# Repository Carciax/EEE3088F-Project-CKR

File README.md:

# EEE3088F-Project-CKR
#Group number 12
# Students: 
Cameron Clark, CLRCAM007; 
Kian Frassek, FRSKIA001; 
Robert Dugmore, DGMROB001; 

## Table of contents
* Description of HAT
* Getting started
  * Introduction
  * Ordering and assembling a HAT
  * Other hardware requirements
  * Hardware connection
  * Software requirements
  * Basic operation of HAT
  * Licensing

# Description of HAT

This sensor PCB HAT connects to an STM32F0 microcontroller and adds additional sensing functionality in the form of an ambient light sensor, a temperature and humidity sensor, an thermistor, and a potentiometer (which could be connected to some form of mechanical sensing system, e.g., a wind vane). The board can be powered directly from USB, or can be powered by an 18650 battery.

# Getting started

## Introduction

This sensor HAT aims to expand the functionality of an STM32F0 microcontroller by adding various sensors. This getting started guide will go over the minimum hardware and software requirements to connect the HAT and start taking measurements.

## Ordering and assembling a HAT

### Ordering from JLC PCB

The HAT has been designed to meet the specifications from JLC PCB (jlcpcb.com). To order a HAT:
* Go to JLC's website (jlcpcb.com)
* Request a quote
* Upload "Final Submission/GROUP12_gerber.zip" as your gerber files
* Select the board specifications (e.g., colour, finish, etc.) as you like. The default options are a reasonable choice.
* Select the option for single sided assembly
* Follow the website instructions until you are prompted to upload a position file and BOM.
* The position file is "Final Submission/GROUP12_position.cpl", and the BOM file is "FINAL_SUBMISSION/GROUP12_bom.csv".
* When asked about footprints that do not have a part number assigned, select "do not place"
* Follow any further instructions from the website for payment and delivery

### Ordering from another board house

If ordering from JLC PCB is not an option for you, you can use the same gerber, position and BOM files to order your HAT from another board house. However, please note the following:
* The HAT may not meet the specifications of another board house.
* The BOM file is unlikely to be in the correct format for another board house.
* The BOM file is unlikely to contain references to the correct components from another board houses's stock; manual selection of components will probably be necessary.

### Additional steps

All male and female headers will have to be obtained and soldered on separately.

It is also recommended to keep track of the issues page of the github to see if there are any outstanding hardware issues with the current iteration of the HAT, which may require manual intervention to solve. 

## Other hardware requirements

### List of required hardware

In addition to the HAT, the following hardware is required:
* an STM32FO microcontoller, with pins connected to 2 1x24-pin male headers spaced -1.524 mm (0.6 in) apart
* A microUSB-B cable
* A 5V USB power supply
* Optional: An 18650 battery
* A computer with an available USB port running Linux or Windows

## Hardware connection

### Microcontroller

The microcontroller should be directly connected to the double-row of females headers labelled "J3". 

### Battery

The 18650 battery (if being used) can be placed directly into the battery holder, taking care to connect it with the correct polarity. The HAT will automatically cut battery power if the voltage drops too low, to protect the battery.

### USB (power supply and data transfer)

The HAT is powered (and the battery is charged) immediately when 5V power is received from the singular USB port. Connecting the USB to a computer enables the start of data transfer to the computer.

### Battery charging

The 18650 battery is charged by the 5V USB power supply. 
The HAT includes red and green charging LEDs. The red LED is powered when the battery is charging, and the green LED is powered when the battery is fully charged.

## Software requirements

### STM32F0 Firmware

The firmware from this repository takes measurements from all sensors at a soft-configurable regular interval. This will need to be uploaded to STM32F0 board.

### Required PC software

The default firmware outputs value over USB serial and requires no additional software.

## Basic operation of HAT

### Reading data on the pc

Data is saved to the EEPROM by default. To send all EEPROM data over the USB connection:
* Connect the USB
* Press switch 1
* LED 1 will flash until all data has been sent
* To abort, press switch 1 again.

### Configuring data read rate

Under normal operation, the HAT takes 1 reading every 60 seconds. This can be soft-configured as follows:
* Press switch 2
* LED 2 will start to flash
* Turn the potentiometer to a desired reading level
* Press 2 again to confirm

## Licensing
MIT License

Copyright (c) 2023 Kian Frassek, Cameron Clark, Robert Dugmore

Permission is hereby granted, free of charge, to any person obtaining a copy
of this software and associated documentation files (the "Software"), to deal
in the Software without restriction, including without limitation the rights
to use, copy, modify, merge, publish, distribute, sublicense, and/or sell
copies of the Software, and to permit persons to whom the Software is
furnished to do so, subject to the following conditions:

The above copyright notice and this permission notice shall be included in all
copies or substantial portions of the Software.

THE SOFTWARE IS PROVIDED "AS IS", WITHOUT WARRANTY OF ANY KIND, EXPRESS OR
IMPLIED, INCLUDING BUT NOT LIMITED TO THE WARRANTIES OF MERCHANTABILITY,
FITNESS FOR A PARTICULAR PURPOSE AND NONINFRINGEMENT. IN NO EVENT SHALL THE
AUTHORS OR COPYRIGHT HOLDERS BE LIABLE FOR ANY CLAIM, DAMAGES OR OTHER
LIABILITY, WHETHER IN AN ACTION OF CONTRACT, TORT OR OTHERWISE, ARISING FROM,
OUT OF OR IN CONNECTION WITH THE SOFTWARE OR THE USE OR OTHER DEALINGS IN THE
SOFTWARE.

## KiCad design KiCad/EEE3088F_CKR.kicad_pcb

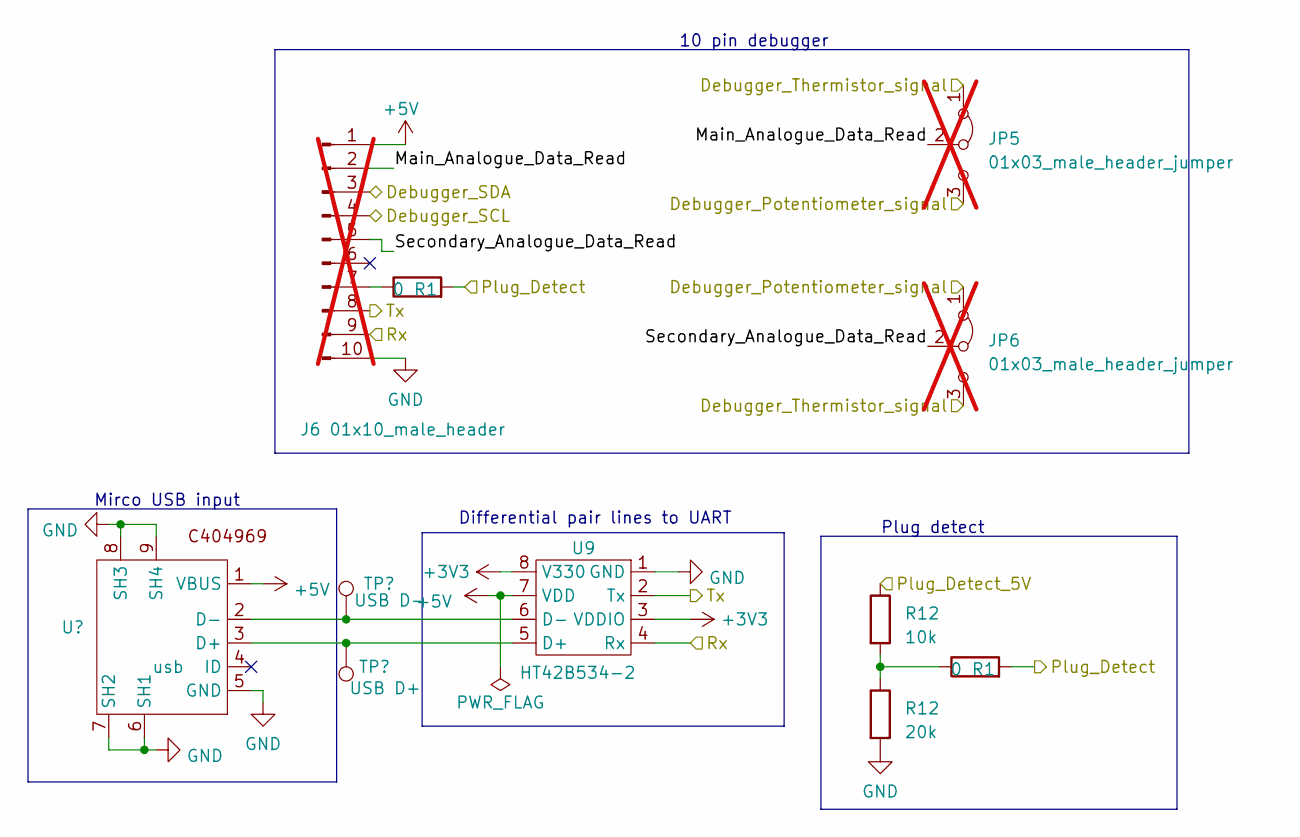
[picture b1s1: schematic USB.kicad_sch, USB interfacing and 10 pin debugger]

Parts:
J6: 01x10_male_header; PinHeader_1x10_P2.54mm_Vertical; not fitted
JP5, JP6: 01x03_male_header_jumper; PinHeader_1x03_P2.54mm_Vertical; not fitted
R1: 0; R0603; Part name 0603WAF0000T5E; JLC code C21189
R12: 20k; R0603; Part name 0603WAF2002T5E; JLC code C4184
TP21: USB D-; Testpoint
TP22: USB D+; Testpoint
U8: usb; MICRO-USB-SMD_MICROXNJ; Part name MicroXNJ; JLC code C404969
U9: HT42B534-2; SOP-8_L4.9-W3.9-P1.27-LS6.0-BL; Part name HT42B534-2; JLC code C493294

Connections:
+3V3: U9.3 (VDDIO), U9.8 (V330); also elsewhere on the board
+5V: J6.1, R1.2, U8.1 (VBUS), U9.7 (VDD); also elsewhere on the board
/Microcontroller/POT_uc: JP5.3 (B), JP6.1 (A); also elsewhere on the board
/Microcontroller/Rx: J6.8, U9.2 (Tx); also elsewhere on the board
/Microcontroller/SCL_uc: J6.4; also elsewhere on the board
/Microcontroller/SDA_uc: J6.3; also elsewhere on the board
/Microcontroller/THM_uc: JP5.1 (A), JP6.3 (B); also elsewhere on the board
/Microcontroller/Tx: J6.9, U9.4 (Rx); also elsewhere on the board
/USB/Main_Analogue_Data_Read: J6.2, JP5.2 (C)
/USB/Secondary_Analogue_Data_Read: J6.5, JP6.2 (C)
unnamed: TP22.1, U8.3 (D+), U9.5 (D+)
unnamed: TP21.1, U8.2 (D-), U9.6 (D-)

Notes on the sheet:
Plug detect
Differential pair lines to UART
10 pin debugger
Mirco USB input

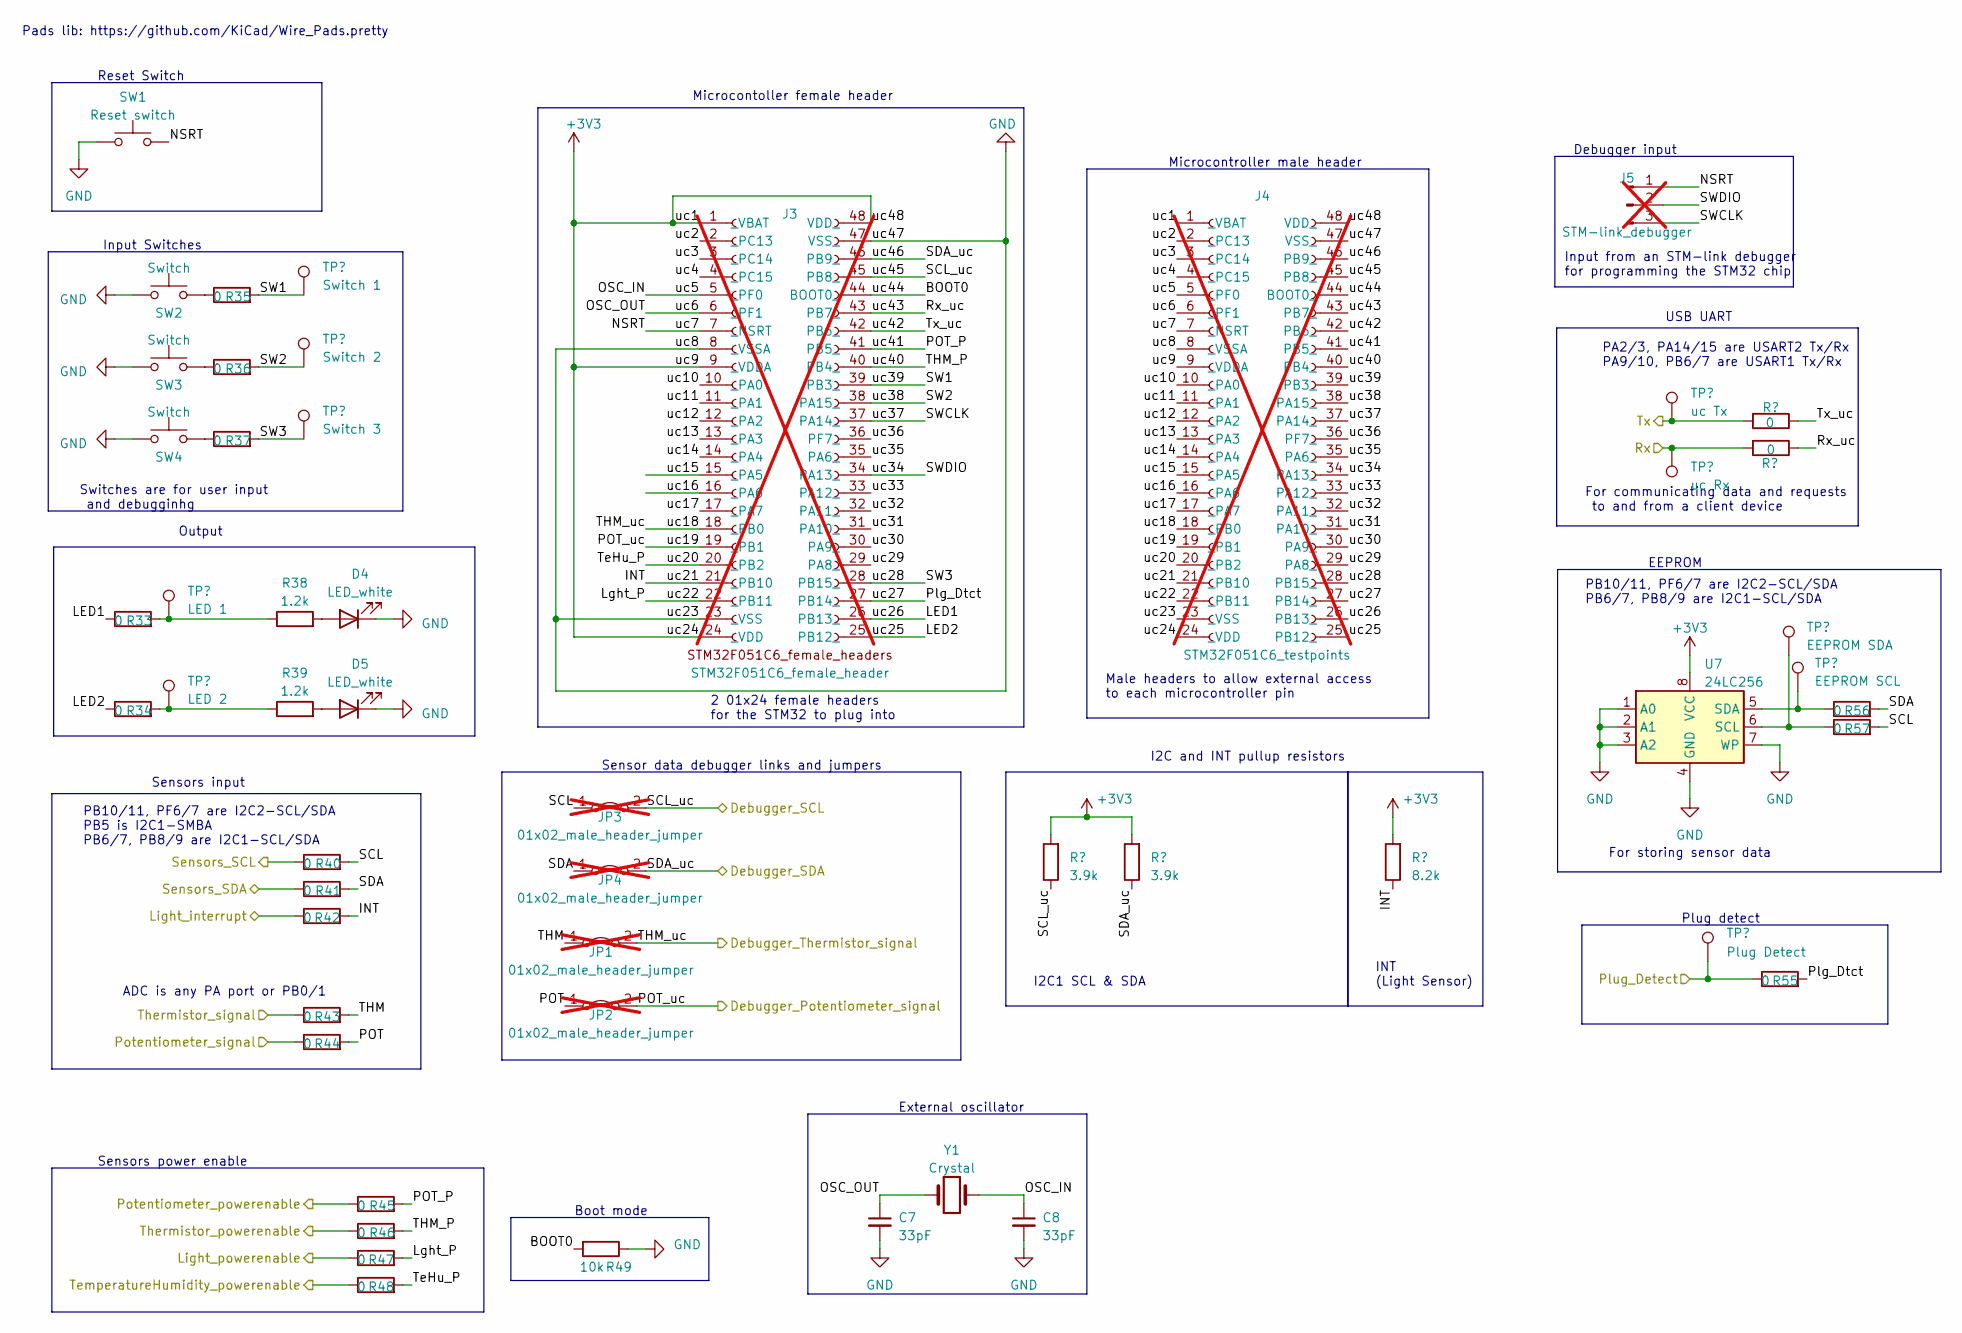
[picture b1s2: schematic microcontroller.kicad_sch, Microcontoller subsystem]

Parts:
C7, C8: 33pF; C0402; Part name 0402CG300J500NT; JLC code C1570
D4, D5: LED_white; LED0805-R-RD; Part name C34499; JLC code C34499
J3: STM32F051C6_female_header; not fitted
J4: STM32F051C6_testpoints; not fitted
J5: STM-link_debugger; PinHeader_1x03_P2.54mm_Vertical; not fitted
JP1, JP2, JP3, JP4: 01x02_male_header_jumper; PinHeader_1x02_P2.54mm_Vertical; not fitted
R33, R34, R35, R36, R37, R40, R41, R42, R43, R44, R45, R46, R47, R48, R53, R54, R55, R56, R57: 0; R0603; Part name 0603WAF0000T5E; JLC code C21189
R38, R39: 1.2k; R0805; Part name 0805W8F3300T5E; JLC code C17630
R49: 10k; R0805; Part name 0805W8F1002T5E; JLC code C17414
R50, R51: 3.9k; R0402; Part name 0402WGF3901TCE; JLC code C51721
R52: 8.2k; R0402; Part name 0402WGF8201TCE; JLC code C25924
SW1: Reset switch; SW-SMD_4P-L5.1-W5.1-P3.70-LS6.5-TL-2; Part name TS-1187A-B-A-B; JLC code C318884
SW2, SW3, SW4: Switch; SW-SMD_4P-L5.1-W5.1-P3.70-LS6.5-TL-2; Part name TS-1187A-B-A-B; JLC code C318884
TP11: LED 1; Testpoint
TP12: LED 2; Testpoint
TP13: Switch 1; Testpoint
TP14: Switch 2; Testpoint
TP15: Switch 3; Testpoint
TP16: uc Tx; Testpoint
TP17: uc Rx; Testpoint
TP18: Plug Detect; Testpoint
TP19: EEPROM SDA; Testpoint
TP20: EEPROM SCL; Testpoint
U7: 24LC256; PDIP-8_L9.3-W6.4-P2.54-LS7.6-BL; Part name 24LC256; JLC code C411624
Y1: Crystal; CRYSTAL-SMD_L11.5-W4.8-LS12.7; Part name X49SM8MSD2SC; JLC code C12674

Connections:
+3V3: J3.1 (_VBAT), J3.9 (_VDDA), J3.24 (_VDD), J3.48 (VDD_), J4.1 (_VBAT), J4.9 (_VDDA), J4.24 (_VDD), J4.48 (VDD_), R50.2, R51.2, R52.2, U7.8 (VCC); also elsewhere on the board
/Microcontroller/BOOT0: J3.44 (BOOT0_), J4.44 (BOOT0_), R49.2
/Microcontroller/INT: J3.21 (_PB10), J4.21 (_PB10), R42.2, R52.1
/Microcontroller/LED1: J3.26 (PB13_), J4.26 (PB13_), R33.1
/Microcontroller/LED2: J3.25 (PB12_), J4.25 (PB12_), R34.1
/Microcontroller/Lght_P: J3.22 (_PB11), J4.22 (_PB11), R47.2
/Microcontroller/Light_powerenable: R47.1; also elsewhere on the board
/Microcontroller/NSRT: J3.7 (_NSRT), J4.7 (_NSRT), J5.1, SW1.2
/Microcontroller/OSC_IN: C8.1, J3.5 (_PF0), J4.5 (_PF0), Y1.2
/Microcontroller/OSC_OUT: C7.1, J3.6 (_PF1), J4.6 (_PF1), Y1.1
/Microcontroller/POT: JP2.1 (A), R44.2
/Microcontroller/POT_P: J3.41 (PB5_), J4.41 (PB5_), R45.2
/Microcontroller/POT_uc: J3.19 (_PB1), J4.19 (_PB1), JP2.2 (B); also elsewhere on the board
/Microcontroller/Plg_Dtct: J3.27 (PB14_), J4.27 (PB14_), R55.2
/Microcontroller/Plug_Detect: R55.1, TP18.1; also elsewhere on the board
/Microcontroller/Potentiometer_powerenable: R45.1; also elsewhere on the board
/Microcontroller/Potentiometer_signal: R44.1; also elsewhere on the board
/Microcontroller/Rx: R54.2, TP17.1; also elsewhere on the board
/Microcontroller/Rx_uc: J3.43 (PB7_), J4.43 (PB7_), R54.1
/Microcontroller/SCL: JP3.1 (A), R40.2, R57.2
/Microcontroller/SCL_uc: J3.45 (PB8_), J4.45 (PB8_), JP3.2 (B), R50.1; also elsewhere on the board
/Microcontroller/SDA: JP4.1 (A), R41.2, R56.2
/Microcontroller/SDA_uc: J3.46 (PB9_), J4.46 (PB9_), JP4.2 (B), R51.1; also elsewhere on the board
/Microcontroller/SW1: J3.39 (PB3_), J4.39 (PB3_), R35.2, TP13.1
/Microcontroller/SW2: J3.38 (PA15_), J4.38 (PA15_), R36.2, TP14.1
/Microcontroller/SW3: J3.28 (PB15_), J4.28 (PB15_), R37.2, TP15.1
/Microcontroller/SWCLK: J3.37 (PA14_), J4.37 (PA14_), J5.3
/Microcontroller/SWDIO: J3.34 (PA13_), J4.34 (PA13_), J5.2
/Microcontroller/THM: JP1.1 (A), R43.2
/Microcontroller/THM_P: J3.40 (PB4_), J4.40 (PB4_), R46.2
/Microcontroller/THM_uc: J3.18 (_PB0), J4.18 (_PB0), JP1.2 (B); also elsewhere on the board
/Microcontroller/TeHu_P: J3.20 (_PB2), J4.20 (_PB2), R48.2
/Microcontroller/TemperatureHumidity_powerenable: R48.1; also elsewhere on the board
/Microcontroller/Thermistor_powerenable: R46.1; also elsewhere on the board
/Microcontroller/Thermistor_signal: R43.1; also elsewhere on the board
/Microcontroller/Tx: R53.2, TP16.1; also elsewhere on the board
/Microcontroller/Tx_uc: J3.42 (PB6_), J4.42 (PB6_), R53.1
/Microcontroller/uc2: J3.2 (_PC13), J4.2 (_PC13)
/Microcontroller/uc3: J3.3 (_PC14), J4.3 (_PC14)
/Microcontroller/uc4: J3.4 (_PC15), J4.4 (_PC15)
/Microcontroller/uc10: J3.10 (_PA0), J4.10 (_PA0)
/Microcontroller/uc11: J3.11 (_PA1), J4.11 (_PA1)
/Microcontroller/uc12: J3.12 (_PA2), J4.12 (_PA2)
/Microcontroller/uc13: J3.13 (_PA3), J4.13 (_PA3)
/Microcontroller/uc14: J3.14 (_PA4), J4.14 (_PA4)
/Microcontroller/uc15: J3.15 (_PA5), J4.15 (_PA5)
/Microcontroller/uc16: J3.16 (_PA6), J4.16 (_PA6)
/Microcontroller/uc17: J3.17 (_PA7), J4.17 (_PA7)
/Microcontroller/uc29: J3.29 (PA8_), J4.29 (PA8_)
/Microcontroller/uc30: J3.30 (PA9_), J4.30 (PA9_)
/Microcontroller/uc31: J3.31 (PA10_), J4.31 (PA10_)
/Microcontroller/uc32: J3.32 (PA11_), J4.32 (PA11_)
/Microcontroller/uc33: J3.33 (PA12_), J4.33 (PA12_)
/Microcontroller/uc35: J3.35 (PA6_), J4.35 (PA6_)
/Microcontroller/uc36: J3.36 (PF7_), J4.36 (PF7_)
/Sensors/Light_SCL: R40.1; also elsewhere on the board
/Sensors/Light_SDA: R41.1; also elsewhere on the board
/Sensors/Light_interrupt: R42.1; also elsewhere on the board
unnamed: D4.2 (A), R38.2
unnamed: D5.2 (A), R39.2
unnamed: R33.2, R38.1, TP11.1
unnamed: R34.2, R39.1, TP12.1
unnamed: R35.1, SW2.2
unnamed: R36.1, SW3.2
unnamed: R37.1, SW4.2
unnamed: R57.1, TP19.1, U7.6 (SCL)
unnamed: R56.1, TP20.1, U7.5 (SDA)

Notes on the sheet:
Input from an STM-link debugger for programming the STM32 chip
Reset Switch
ADC is any PA port or PB0/1
Input Switches
I2C and INT pullup resistors
For communicating data and requests to and from a client device
Pads lib: https://github.com/KiCad/Wire_Pads.pretty
2 01x24 female headers for the STM32 to plug into
PA2/3, PA14/15 are USART2 Tx/Rx PA9/10, PB6/7 are USART1 Tx/Rx
External oscillator
Microcontroller male header
EEPROM
Boot mode
USB UART
Sensors input
Microcontoller female header
PB10/11, PF6/7 are I2C2-SCL/SDA PB6/7, PB8/9 are I2C1-SCL/SDA
Male headers to allow external access to each microcontroller pin
Switches are for user input and debugginhg
Sensor data debugger links and jumpers
For storing sensor data
Plug detect
I2C1 SCL & SDA
Output
INT (Light Sensor)
Debugger input
PB10/11, PF6/7 are I2C2-SCL/SDA PB5 is I2C1-SMBA PB6/7, PB8/9 are I2C1-SCL/SDA
Sensors power enable

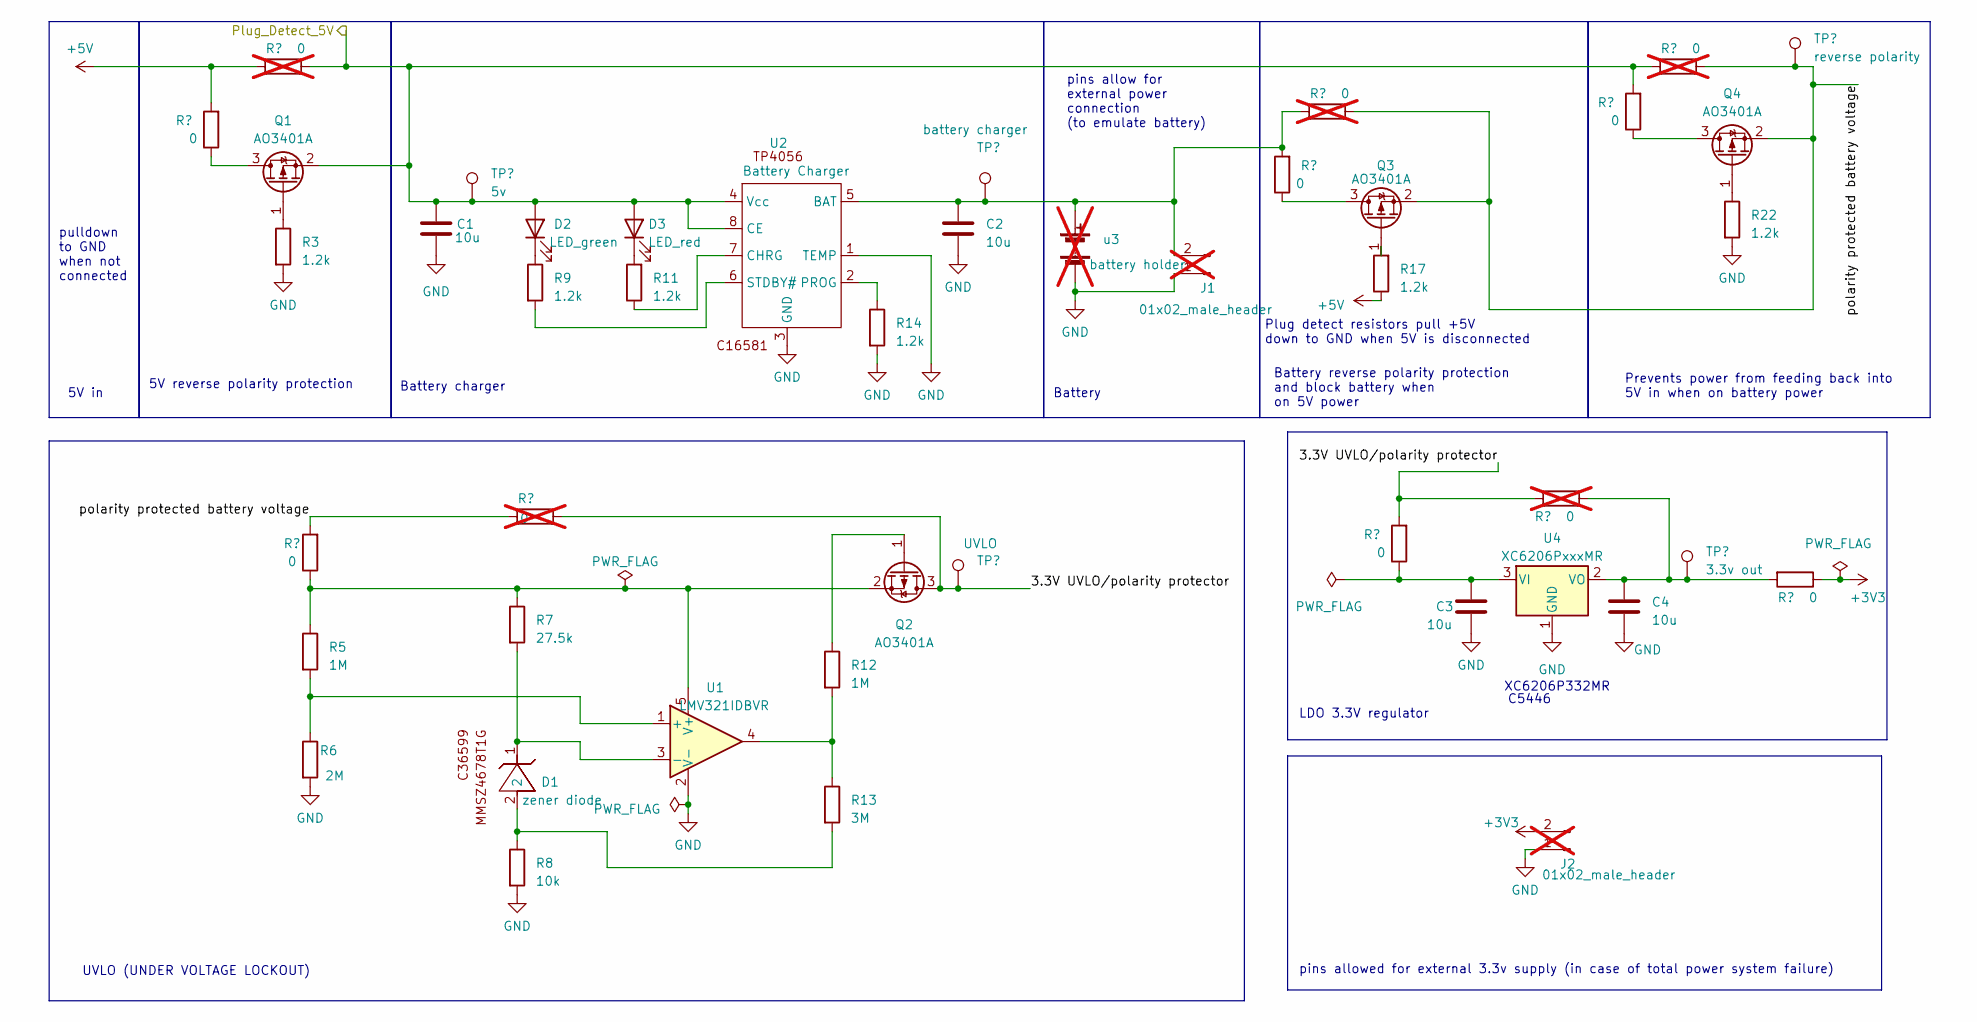
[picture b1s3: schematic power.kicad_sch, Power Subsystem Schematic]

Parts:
C1, C2, C3, C4: 10u; C0603; Part name CL10A106KP8NNNC; JLC code C19702
D1: zener diode; SOD-123_L2.8-W1.8-LS3.7-RD; Part name MMSZ4678T18; JLC code C36599
D2: LED_green; LED0603-RD; Part name 19-217/GHC-YR1S2/3T; JLC code C72043
D3: LED_red; LED0603-RD; Part name KT-0603R; JLC code C2286
J1, J2: 01x02_male_header; PinHeader_1x02_P2.54mm_Vertical; not fitted
Q1, Q2, Q3, Q4: AO3401A; SOT-23_L2.9-W1.3-P1.90-LS2.4-BR; Part name AO3401A; JLC code C15127
R1, R4, R15, R18, R20, R23: 0; R0603; Part name 0603WAF0000T5E; JLC code C21189
R2, R10, R16, R19, R21: 0; R0603; Part name 0603WAF0000T5E; JLC code C21189; not fitted
R3, R9, R11, R14, R17, R22: 1.2k; R0805; Part name 0805W8F3300T5E; JLC code C17630
R5, R12: 1M; R0805; Part name 0805W8F1004T5E; JLC code C17514
R6: 2M; R0805; Part name 0805W8F2004T5E; JLC code C26112
R7: 27.5k; R0805; Part name 0805W8F2702T5E; JLC code C17593
R8: 10k; R0805; Part name 0805W8F1002T5E; JLC code C17414
R13: 3M; R0603; Part name 0603WAF3004T5E; JLC code C23156
TP1: 5v; Testpoint
TP2: UVLO; Testpoint
TP3: battery charger; Testpoint
TP4: 3.3v out; Testpoint
TP5: reverse polarity; Testpoint
U1: LMV321IDBVR; SOT-23-5_L3.0-W1.7-P0.95-LS2.8-BR; Part name LMV321; JLC code C7972
U2: Battery Charger; ESOP-8_L4.9-W3.9-P1.27-LS6.0-BL-EP; Part name TP4056; JLC code C16581
U4: XC6206PxxxMR; SOT-23-3_L2.9-W1.6-P1.90-LS2.8-BR; Part name XC6206P332MR; JLC code C5446
u3: battery holder; BATTERY-SMD_18650-1S-L77.1-W20.7-1; Part name BH-18650-B1BA002; JLC code C2988620; not fitted

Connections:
+3V3: J2.2, R23.1; also elsewhere on the board
+5V: R1.2, R2.2, R17.1; also elsewhere on the board
/Power/3.3V UVLO/polarity protector: Q2.3 (D), R10.2, R18.2, R19.2, TP2.1
/Power/Plug_Detect_5V: C1.1, D2.2 (A), D3.2 (A), Q1.2 (S), R2.1, R20.2, R21.2, TP1.1, U2.4 (Vcc), U2.8 (CE); also elsewhere on the board
/Power/polarity protected battery voltage: Q3.2 (S), Q4.2 (S), R4.2, R10.1, R16.1, R21.1, TP5.1
unnamed: D1.2, R8.1, R13.2
unnamed: D2.1 (K), R9.1
unnamed: D3.1 (K), R11.2
unnamed: C2.1, J1.2, R15.2, R16.2, TP3.1, U2.5 (BAT), u3.1 (+)
unnamed: Q1.1 (G), R3.1
unnamed: Q2.2 (S), R4.1, R5.1, R7.1, U1.5 (V+)
unnamed: Q3.3 (D), R15.1
unnamed: Q3.1 (G), R17.2
unnamed: Q4.3 (D), R20.1
unnamed: Q4.1 (G), R22.1
unnamed: R5.2, R6.1, U1.1 (+)
unnamed: D1.1, R7.2, U1.3 (-)
unnamed: R11.1, U2.7 (CHRG)
unnamed: R14.1, U2.2 (PROG)
unnamed: R9.2, U2.6 (STDBY#)
unnamed: C3.1, R18.1, U4.3 (VI)
unnamed: C4.1, R19.1, R23.2, TP4.1, U4.2 (VO)

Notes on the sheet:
C5446
5V reverse polarity protection
5V in
UVLO (UNDER VOLTAGE LOCKOUT)
Battery charger
pulldown to GND when not connected
XC6206P332MR
pins allow for external power connection (to emulate battery)
Plug detect resistors pull +5V down to GND when 5V is disconnected
LDO 3.3V regulator
pins allowed for external 3.3v supply (in case of total power system failure)
Battery reverse polarity protection and block battery when on 5V power
Prevents power from feeding back into 5V in when on battery power
Battery

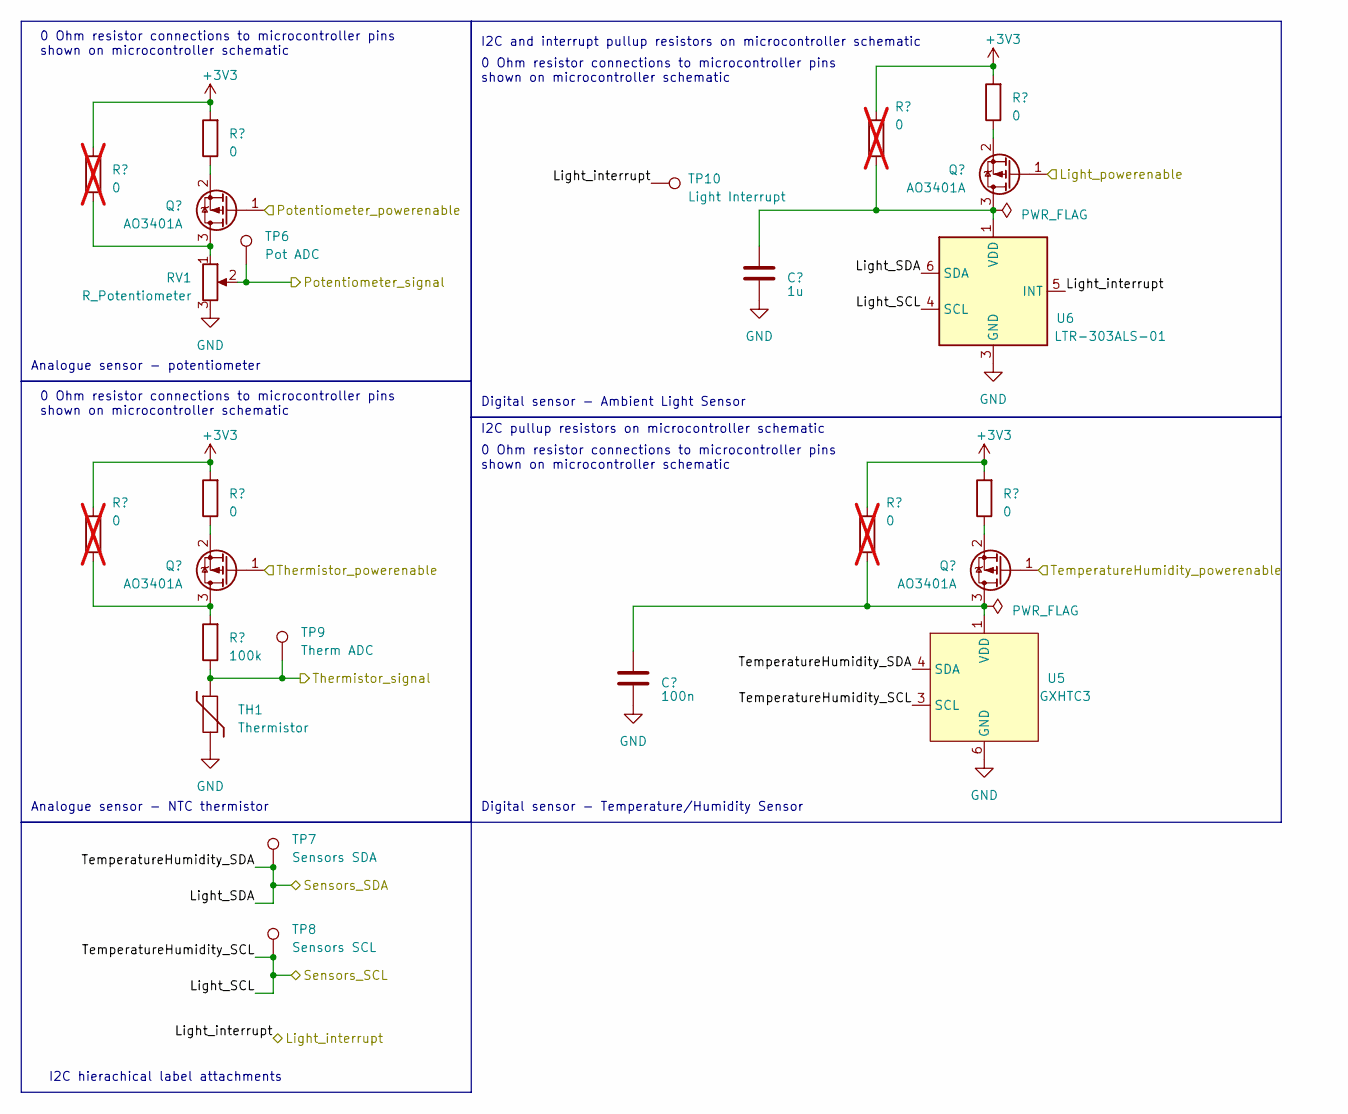
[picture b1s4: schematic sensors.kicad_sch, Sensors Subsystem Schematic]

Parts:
C5: 100n; C0402; Part name CL05B104KO5NNNC; JLC code C1525
C6: 1u; C0402; Part name CL05A105KA5NQNC; JLC code C52923
Q5, Q6, Q7, Q8: AO3401A; SOT-23_L2.9-W1.3-P1.90-LS2.4-BR; Part name AO3401A; JLC code C15127
R24, R25, R29, R30: 0; R0603; Part name 0603WAF0000T5E; JLC code C21189; not fitted
R26, R27, R31, R32: 0; R0603; Part name 0603WAF0000T5E; JLC code C21189
R28: 100k; R1206; Part name 1206W4F1003T5E; JLC code C17900
RV1: R_Potentiometer; RES-ADJ-TH_RK09K1130AJ3; Part name RK09K1130AJ3; JLC code C388854
TH1: Thermistor; R0402; Part name NCP15WF104F03RC; JLC code C77130
TP6: Pot ADC; Testpoint
TP7: Sensors SDA; Testpoint
TP8: Sensors SCL; Testpoint
TP9: Therm ADC; Testpoint
TP10: Light Interrupt; Testpoint
U5: GXHTC3; DFN-6_L2.0-W2.0-P0.50-BL-EP; Part name GXHTC3; JLC code C2837688
U6: LTR-303ALS-01; SOT-363_L2.0-W1.3-P0.65-LS2.1-BL; Part name LTR-303ALS-01; JLC code C364577

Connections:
+3V3: R24.2, R25.2, R26.2, R27.2, R29.2, R30.2, R31.2, R32.2; also elsewhere on the board
/Microcontroller/Light_powerenable: Q8.1 (G); also elsewhere on the board
/Microcontroller/Potentiometer_powerenable: Q5.1 (G); also elsewhere on the board
/Microcontroller/Potentiometer_signal: RV1.2, TP6.1; also elsewhere on the board
/Microcontroller/TemperatureHumidity_powerenable: Q7.1 (G); also elsewhere on the board
/Microcontroller/Thermistor_powerenable: Q6.1 (G); also elsewhere on the board
/Microcontroller/Thermistor_signal: R28.1, TH1.1, TP9.1; also elsewhere on the board
/Sensors/Light_SCL: TP8.1, U5.3 (SCL), U6.4 (SCL); also elsewhere on the board
/Sensors/Light_SDA: TP7.1, U5.4 (SDA), U6.6 (SDA); also elsewhere on the board
/Sensors/Light_interrupt: TP10.1, U6.5 (INT); also elsewhere on the board
unnamed: Q5.3 (D), R24.1, RV1.1
unnamed: Q5.2 (S), R26.1
unnamed: Q6.3 (D), R25.1, R28.2
unnamed: Q6.2 (S), R27.1
unnamed: C5.1, Q7.3 (D), R29.1, U5.1 (VDD)
unnamed: Q7.2 (S), R31.1
unnamed: C6.1, Q8.3 (D), R30.1, U6.1 (VDD)
unnamed: Q8.2 (S), R32.1

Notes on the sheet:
Digital sensor - Ambient Light Sensor
0 Ohm resistor connections to microcontroller pins shown on microcontroller schematic
I2C hierachical label attachments
Analogue sensor - NTC thermistor
I2C pullup resistors on microcontroller schematic
I2C and interrupt pullup resistors on microcontroller schematic
Analogue sensor - potentiometer
Digital sensor - Temperature/Humidity Sensor

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
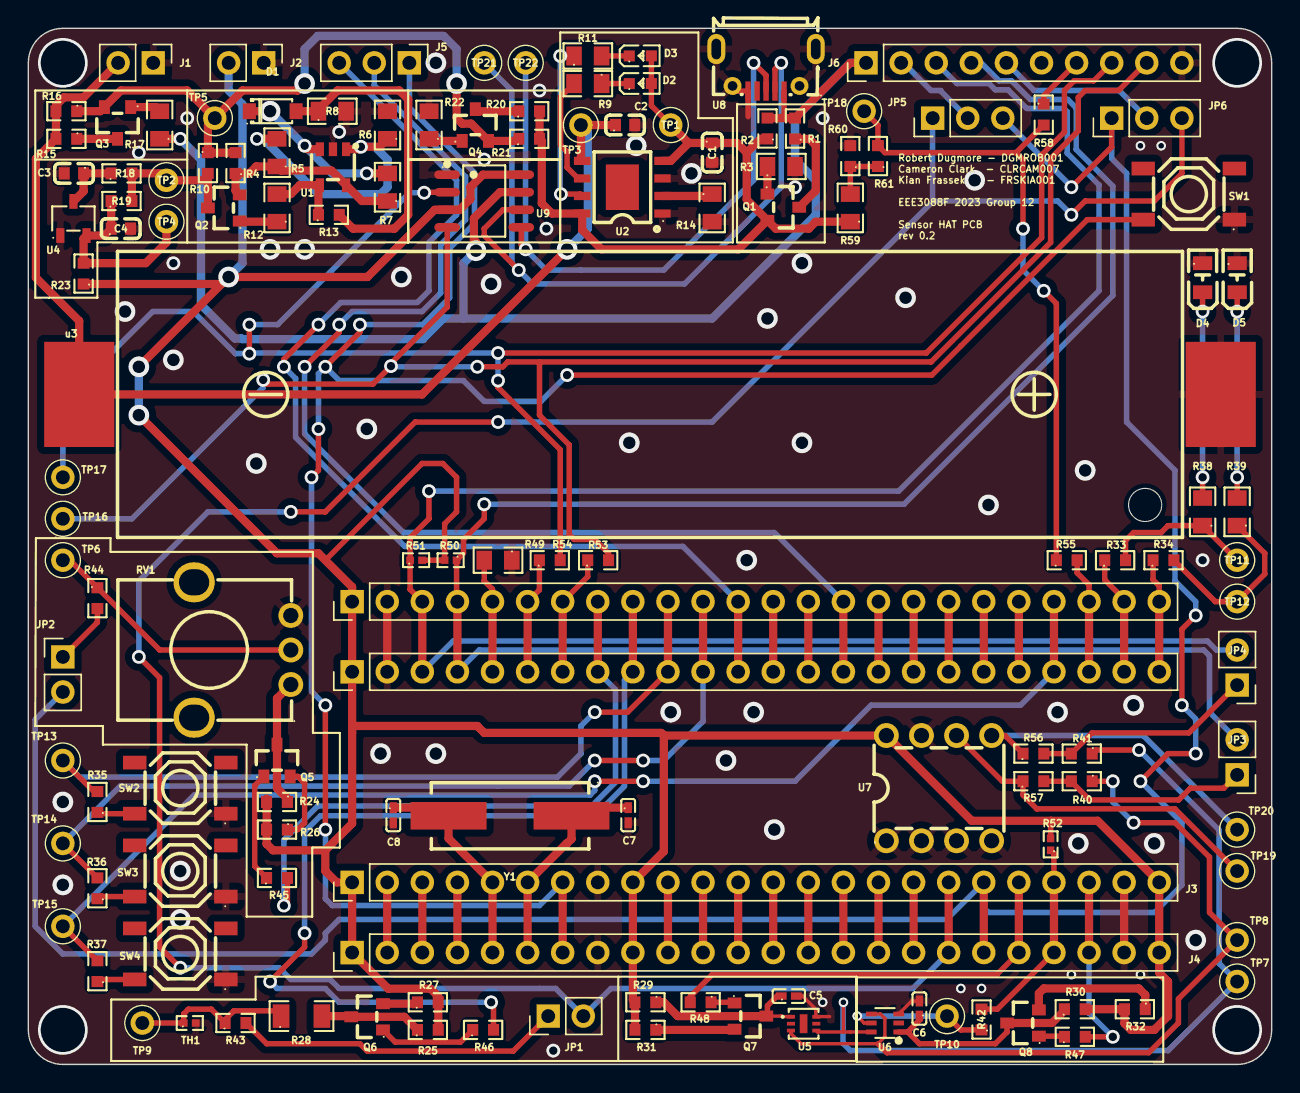
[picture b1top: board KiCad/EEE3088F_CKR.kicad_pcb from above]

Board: 2 copper layers, 90.0 x 75.0 mm, 132 parts (0 on the bottom side), 106 nets.

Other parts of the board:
R58, R61: 0; R0603
R59: 10k; R0805
R60: 20k; R0603

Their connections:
/Microcontroller/Plug_Detect: R58.2, R61.2; also elsewhere on the board
/Power/Plug_Detect_5V: R59.1; also elsewhere on the board
unnamed: R59.2, R60.1, R61.1

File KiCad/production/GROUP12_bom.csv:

Designator,Footprint,Quantity,Value,LCSC Part #
B1,BATTERY-SMD_18650-1S-L77.1-W20.7-1,1,battery holder,DNP
"C1, C2, C3, C4",C0603,4,10u,C19702
C5,C0402,1,100n,C1525
C6,C0402,1,1u,C52923
"C7, C8",C0402,2,33pF,C1570
D1,SOD-123_L2.8-W1.8-LS3.7-RD,1,zener diode,C36599
D2,LED0603-RD,1,LED_green,C72043
D3,LED0603-RD,1,LED_red,C2286
"D4, D5",LED0805-R-RD,2,LED_white,C34499
"J1, J2",PinHeader_1x02_P2.54mm_Vertical,2,01x02_male_header,DNP
J3,STM32F051C6_female_header,1,STM32F051C6_female_header,DNP
J4,STM32F051C6_testpoints,1,STM32F051C6_testpoints,DNP
J5,PinHeader_1x03_P2.54mm_Vertical,1,STM-link_debugger,DNP
J6,PinHeader_1x10_P2.54mm_Vertical,1,01x10_male_header,DNP
"JP1, JP2, JP3, JP4",PinHeader_1x02_P2.54mm_Vertical,4,01x02_male_header_jumper,DNP
"JP5, JP6",PinHeader_1x03_P2.54mm_Vertical,2,01x03_male_header_jumper,DNP
"Q1, Q2, Q3, Q4, Q5, Q6, Q7, Q8",SOT-23_L2.9-W1.3-P1.90-LS2.4-BR,8,AO3401A,C15127
"R1, R15, R18, R20, R23, R26, R27, R31, R32, R33, R34, R35, R36, R37, R4, R40, R41, R42, R43, R44, R45, R46, R47, R48, R53, R54, R55, R56, R57, R58, R61",R0603,31,0,C21189
"R10, R16, R19, R2, R21, R24, R25, R29, R30",R0603,9,0,DNP
"R11, R14, R17, R22, R3, R38, R39, R9",R0805,8,1.2k,C17630
"R12, R5",R0805,2,1M,C17514
R13,R0603,1,3M,C26112
R28,R1206,1,100k,C17593
"R49, R59, R8",R0805,3,10k,C17414
"R50, R51",R0402,2,3.9k,C23156
R52,R0402,1,8.2k,C17900
R6,R0805,1,2M,C51721
R60,R0603,1,20k,C25924
R7,R0805,1,27.5k,C4184
RV1,RES-ADJ-TH_RK09K1130AJ3,1,R_Potentiometer,C388854
SW1,SW-SMD_4P-L5.1-W5.1-P3.70-LS6.5-TL-2,1,Reset switch,C318884
"SW2, SW3, SW4",SW-SMD_4P-L5.1-W5.1-P3.70-LS6.5-TL-2,3,Switch,C318884
TH1,R0402,1,Thermistor,C77130
TP1,Testpoint,1,5v,DNP
TP10,Testpoint,1,Light Interrupt,DNP
TP11,Testpoint,1,LED 1,DNP
TP12,Testpoint,1,LED 2,DNP
TP13,Testpoint,1,Switch 1,DNP
TP14,Testpoint,1,Switch 2,DNP
TP15,Testpoint,1,Switch 3,DNP
TP16,Testpoint,1,uc Tx,DNP
TP17,Testpoint,1,uc Rx,DNP
TP18,Testpoint,1,Plug Detect,DNP
TP19,Testpoint,1,EEPROM SDA,DNP
TP2,Testpoint,1,UVLO,DNP
TP20,Testpoint,1,EEPROM SCL,DNP
TP21,Testpoint,1,USB D-,DNP
TP22,Testpoint,1,USB D+,DNP
TP3,Testpoint,1,battery charger,DNP
TP4,Testpoint,1,3.3v out,DNP
TP5,Testpoint,1,reverse polarity ,DNP
TP6,Testpoint,1,Pot ADC,DNP
TP7,Testpoint,1,Sensors SDA,DNP
TP8,Testpoint,1,Sensors SCL,DNP
TP9,Testpoint,1,Therm ADC,DNP
U1,SOT-23-5_L3.0-W1.7-P0.95-LS2.8-BR,1,LMV321IDBVR,C7972
U2,ESOP-8_L4.9-W3.9-P1.27-LS6.0-BL-EP,1,Battery Charger,C16581
U4,SOT-23-3_L2.9-W1.6-P1.90-LS2.8-BR,1,XC6206PxxxMR,C5446
U5,DFN-6_L2.0-W2.0-P0.50-BL-EP,1,GXHTC3,C2837688
U6,SOT-363_L2.0-W1.3-P0.65-LS2.1-BL,1,LTR-303ALS-01,C364577
U7,PDIP-8_L9.3-W6.4-P2.54-LS7.6-BL,1,24LC256,C411624
U8,MICRO-USB-SMD_MICROXNJ,1,usb,C404969
U9,SOP-8_L4.9-W3.9-P1.27-LS6.0-BL,1,HT42B534-2,C493294
Y1,CRYSTAL-SMD_L11.5-W4.8-LS12.7,1,Crystal,C12674
